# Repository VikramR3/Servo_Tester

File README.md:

# Servo Tester

A 2-layer PCB that exercises an RC servo without a microcontroller: an NE555 astable
generates the servo pulse train, and a 100 kΩ potentiometer sweeps the pulse width to
drive the horn across its full travel. Designed in KiCad 9.

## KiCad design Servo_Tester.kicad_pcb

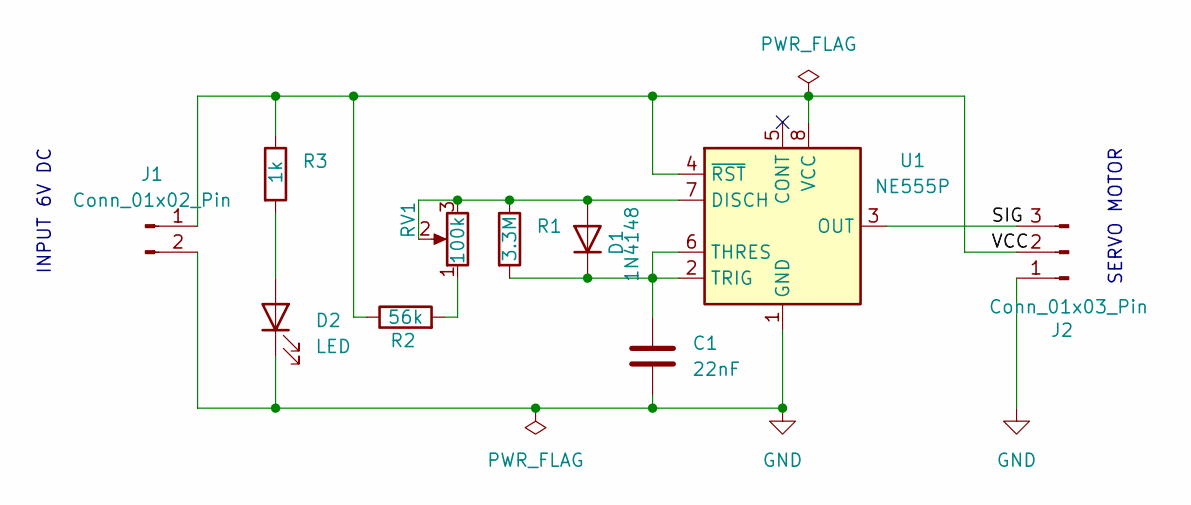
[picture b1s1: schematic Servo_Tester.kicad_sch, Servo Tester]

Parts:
C1: 22nF; C_Disc_D4.3mm_W1.9mm_P5.00mm
D1: 1N4148; D_DO-35_SOD27_P7.62mm_Horizontal
D2: LED; LED_D3.0mm
J1: Conn_01x02_Pin; PinHeader_1x02_P2.54mm_Horizontal
J2: Conn_01x03_Pin; PinHeader_1x03_P2.54mm_Horizontal
R1: 3.3M; R_Axial_DIN0204_L3.6mm_D1.6mm_P7.62mm_Horizontal
R2: 56k; R_Axial_DIN0204_L3.6mm_D1.6mm_P7.62mm_Horizontal
R3: 1k; R_Axial_DIN0204_L3.6mm_D1.6mm_P7.62mm_Horizontal
RV1: 100k; Potentiometer_Alps_RK163_Single_Horizontal
U1: NE555P; DIP-8_W7.62mm

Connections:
/SIG: J2.3, U1.3 (OUT)
/VCC: J1.1, J2.2, R2.1, R3.1, U1.4 (~RST), U1.8 (VCC)
GND: C1.2, D2.1 (K), J1.2, J2.1, U1.1 (GND)
unnamed: D1.2 (A), R1.1, RV1.2, RV1.3, U1.7 (DISCH)
unnamed: C1.1, D1.1 (K), R1.2, U1.2 (TRIG), U1.6 (THRES)
unnamed: D2.2 (A), R3.2
unnamed: R2.2, RV1.1

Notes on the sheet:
INPUT 6V DC
SERVO MOTOR

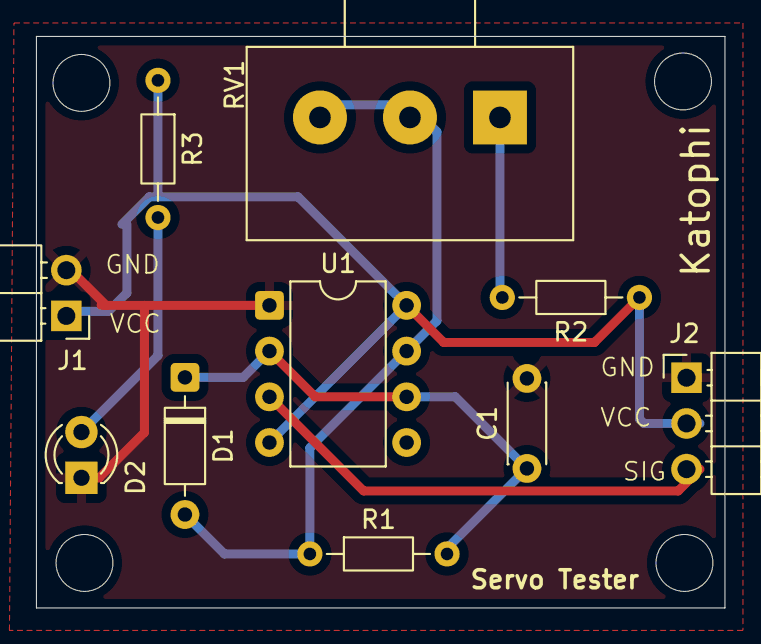
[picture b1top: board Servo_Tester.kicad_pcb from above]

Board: 2 copper layers, 38.2 x 31.8 mm, 10 parts (0 on the bottom side), 7 nets.

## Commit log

2025-06-22 Servo tester: NE555 astable with pot-controlled pulse width
    Two-layer 38.2 x 31.8 mm board. NE555 astable with a split charge and
    discharge path: RV1 100k plus R2 56k sets the pulse width through a
    1N4148 steering diode, R1 3.3M sets the frame gap, C1 22nF times both.
    2-pin power input on J1, 3-pin servo header on J2, power LED on D2.
